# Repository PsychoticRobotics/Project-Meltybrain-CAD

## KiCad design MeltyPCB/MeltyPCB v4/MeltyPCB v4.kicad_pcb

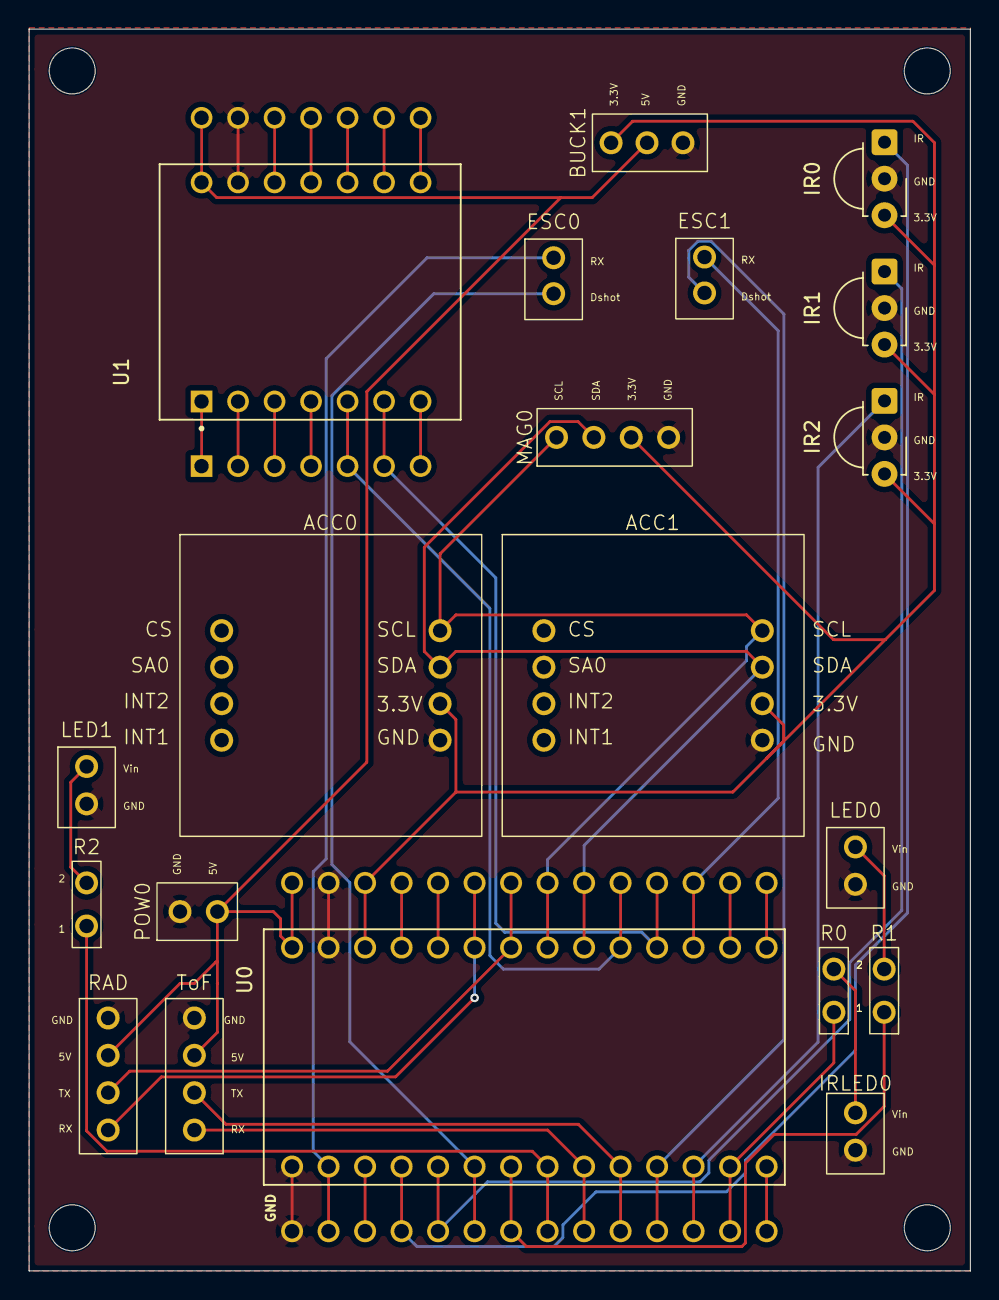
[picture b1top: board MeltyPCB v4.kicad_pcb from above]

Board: 2 copper layers, 65.5 x 86.4 mm, 20 parts (0 on the bottom side), 21 nets.

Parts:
ACC0, ACC1: Accelerometer; Accelerometer (Through Holes)
BUCK1: Buck Converter
ESC0, ESC1: Vortex ESC
IR0, IR1, IR2: TSOP384xx; Vishay_MINICAST-3Pin
IRLED0: IR LED; LED
LED0, LED1: LED
MAG0: Magnetometer
POW0: Power
R0, R1, R2: 470 Ohm; Resistor
RAD: Radio Receiver; Receiver
ToF: TFmini IR Receiver; Receiver
U0: Teensy 4.0; Teensy 4.0 (Simplified) (Extra Holes)
U1: XIAO_ESP32_S3; XIAO_ESP32_S3 (Extra Holes)

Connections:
+3.3V: ACC0.7 (3.3V), ACC1.7 (3.3V), BUCK1.1 (3.3V), IR0.3 (Vs), IR1.3 (Vs), IR2.3 (Vs), MAG0.3 (3.3V), U0.3.3V_2
+5V: BUCK1.2 (5V), POW0.1 (5V), RAD.2 (5V), ToF.2 (5V), U0.VIN, U1.14 (5V)
/Dshot0: ESC0.2 (Dshot), U0.4
/Dshot1: ESC1.2 (Dshot), U0.9
/IR0: IR0.1 (OUT), U0.2
/IR1: IR1.1 (OUT), U0.3
/IR2: IR2.1 (OUT), U0.10
/IRLED: IRLED0.1 (Vin), R0.1, R0.2, U0.11
/LED0: LED0.1 (Vin), R1.1, R1.2, U0.5
/LED1: LED1.1 (Vin), R2.1, R2.2, U0.6
/RX1: ESC0.1 (RX), U0.0
/RX2: ToF.4 (RX), U0.7
/RX3: ESC1.1 (RX), U0.15
/RX5: RAD.4 (RX), U0.21
/SCL0: ACC0.5 (SCL), ACC1.5 (SCL), MAG0.1 (SCL), U0.19
/SCL1: U0.16, U1.6 (D5/GPIO6)
/SDA0: ACC0.6 (SDA), ACC1.6 (SDA), MAG0.2 (SDA), U0.18
/SDA1: U0.17, U1.5 (D4/GPIO5)
/TX2: ToF.3 (TX), U0.8
/TX5: RAD.3 (TX), U0.20
GND: ACC0.8 (GND), ACC1.8 (GND), BUCK1.3 (GND), IR0.2 (GND), IR1.2 (GND), IR2.2 (GND), IRLED0.2 (GND), LED0.2 (GND), LED1.2 (GND), MAG0.4 (GND), POW0.2 (GND), RAD.1 (GND), ToF.1 (GND), U0.G1, U0.G3, U1.13 (GND)

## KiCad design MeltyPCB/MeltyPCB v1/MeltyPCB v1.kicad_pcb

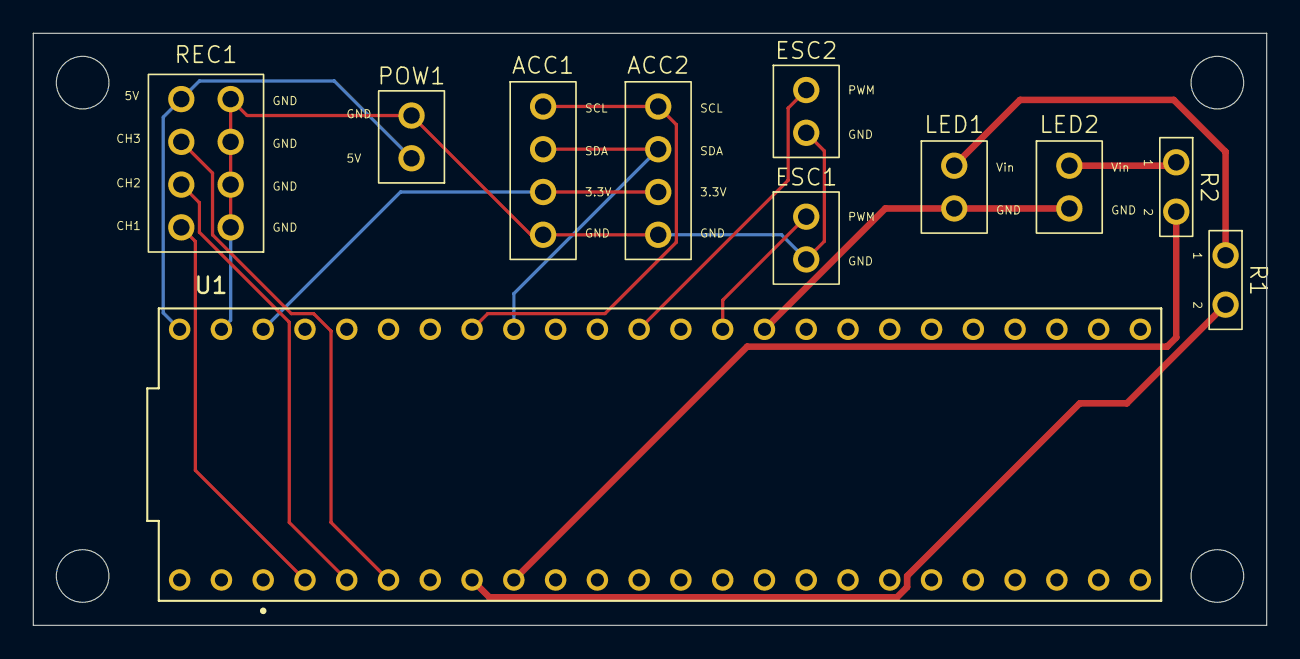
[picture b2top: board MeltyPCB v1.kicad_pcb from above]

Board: 2 copper layers, 75.0 x 36.0 mm, 11 parts (0 on the bottom side), 12 nets.

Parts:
ACC1, ACC2: Accelerometer
ESC1, ESC2: ESC
LED1, LED2: LED
POW1: Power
R1, R2: 470 Ohm; Resistor
REC1: Reciever
U1: DEV-16771 (Teensy 4.1); Teensy 4.1 (Through Holes) (Simplified)

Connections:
+3V3: ACC1.3 (3.3V), ACC2.3 (3.3V), U1.3.3V_1 (3.3V), U1.3.3V_2 (3.3V)
+5V: POW1.1 (5V), REC1.4 (5V)
/CH1: REC1.1 (CH1), U1.2 (OUT2)
/CH2: REC1.2 (CH2), U1.3 (LRCLK2)
/CH3: REC1.3 (CH3), U1.4 (BCLK2)
/ESC1: ESC1.1 (PWM), U1.13 (SCK)
/ESC2: ESC2.1 (PWM), U1.15 (A1)
/LED1: LED1.1 (Vin), R1.1, R1.2, U1.6 (OUT1D)
/LED2: LED2.1 (Vin), R2.1, R2.2, U1.7 (RX2)
/SCL: ACC1.1 (SCL), ACC2.1 (SCL), U1.19 (A5)
/SDA: ACC1.2 (SDA), ACC2.2 (SDA), U1.18 (A4)
GND: ACC1.4 (GND), ACC2.4 (GND), ESC1.2 (GND), ESC2.2 (GND), LED1.2 (GND), LED2.2 (GND), POW1.2 (GND), REC1.5 (GND), REC1.6 (GND), REC1.7 (GND), REC1.8 (GND), U1.GND1 (GND), U1.GND2 (GND), U1.GND3 (GND)

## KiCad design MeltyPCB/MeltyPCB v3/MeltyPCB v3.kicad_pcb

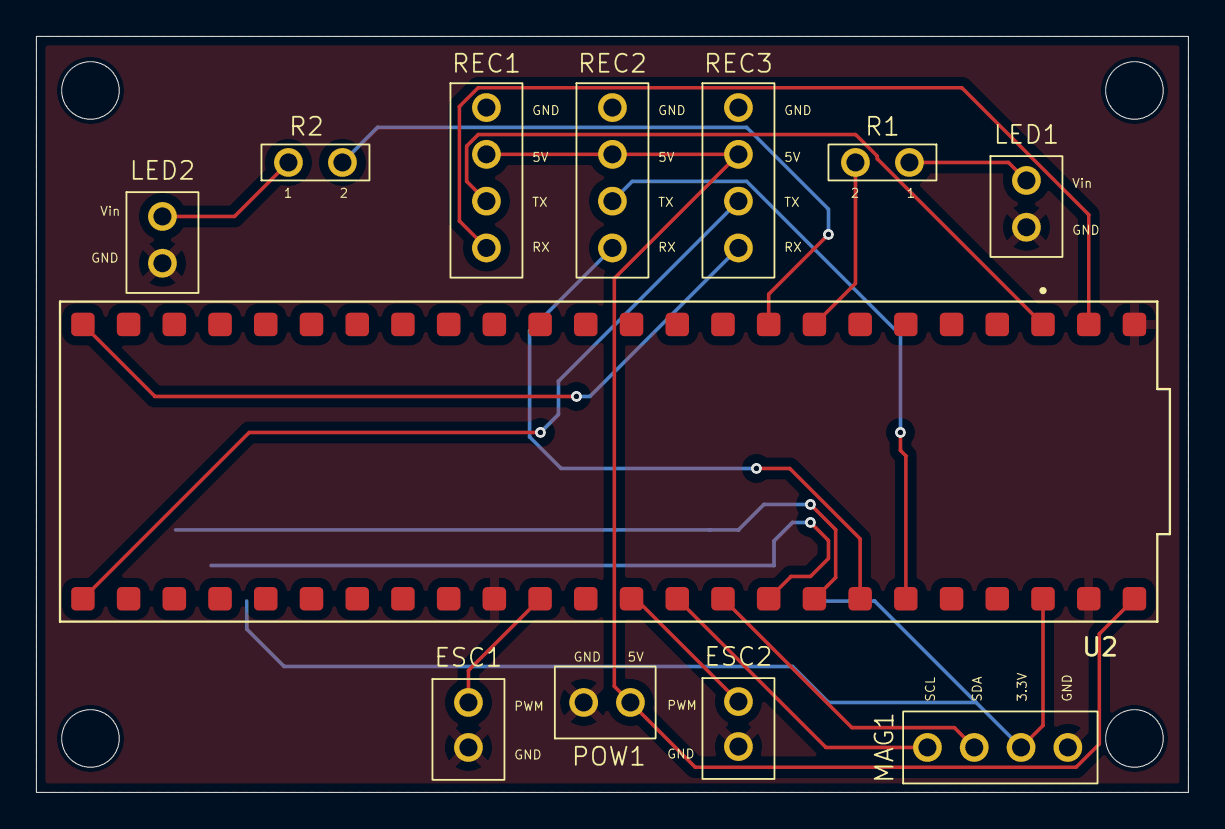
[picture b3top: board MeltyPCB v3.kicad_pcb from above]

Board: 2 copper layers, 64.0 x 42.0 mm, 14 parts (0 on the bottom side), 17 nets.

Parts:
ACC1, ACC2: Accelerometer
ESC1, ESC2: ESC
LED1, LED2: LED
MAG1: Magnetometer
POW1: Power
R1, R2: 470 Ohm; Resistor
REC1, REC2, REC3: Receiver
U2: DEV-16771 (Teensy 4.1); Teensy 4.1 (Pads) (Simplified)

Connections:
+3.3V: ACC1.7 (3.3V), ACC2.7 (3.3V), MAG1.3 (3.3V), U2.3.3V_1 (3.3V), U2.3.3V_2 (3.3V)
+5V: POW1.1 (5V), REC1.2 (5V), REC2.2 (5V), REC3.2 (5V), U2.VIN
/ESC1: ESC1.1 (PWM), U2.13 (SCK)
/ESC2: ESC2.1 (PWM), U2.15 (A1)
/LED1: LED1.1 (Vin), R1.1, R1.2, U2.6 (OUT1D)
/LED2: LED2.1 (Vin), R2.1, R2.2, U2.7 (RX2)
/RX: REC1.4 (RX), U2.0 (RX1)
/RX5: REC2.4 (RX), U2.20 (A6)
/RX6: REC3.4 (RX), U2.32 (OUT1B)
/SCL: ACC1.5 (SCL), ACC2.5 (SCL), U2.19 (A5)
/SCL2: MAG1.1 (SCL), U2.16 (A2)
/SDA: ACC1.6 (SDA), ACC2.6 (SDA), U2.18 (A4)
/SDA2: MAG1.2 (SDA), U2.17 (A3)
/TX: REC1.3 (TX), U2.1 (TX1)
/TX5: REC2.3 (TX), U2.21 (A7)
/TX6: REC3.3 (TX), U2.33 (MCLK2)
GND: ACC1.8 (GND), ACC2.8 (GND), ESC1.2 (GND), ESC2.2 (GND), LED1.2 (GND), LED2.2 (GND), MAG1.4 (GND), POW1.2 (GND), REC1.1 (GND), REC2.1 (GND), REC3.1 (GND), U2.GND1 (GND), U2.GND2 (GND), U2.GND3 (GND)

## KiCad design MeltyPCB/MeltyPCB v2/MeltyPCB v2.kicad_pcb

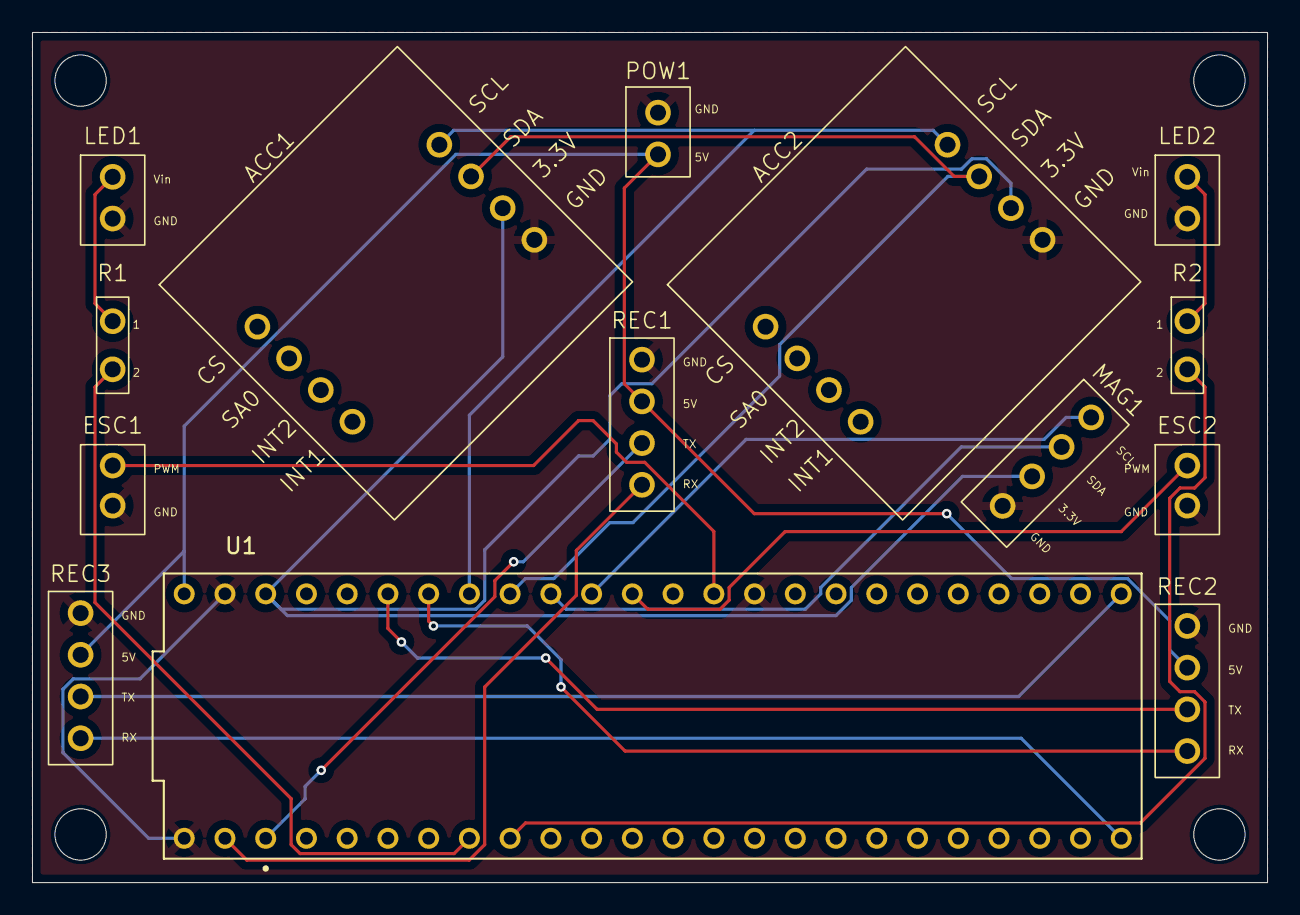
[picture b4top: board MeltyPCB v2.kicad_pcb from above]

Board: 2 copper layers, 77.0 x 53.0 mm, 14 parts (0 on the bottom side), 17 nets.

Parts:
ACC1, ACC2: Accelerometer; Accelerometer (v2)
ESC1, ESC2: ESC
LED1, LED2: LED
MAG1: Magnetometer
POW1: Power
R1, R2: 470 Ohm; Resistor
REC1, REC2, REC3: Receiver
U1: DEV-16771 (Teensy 4.1); Teensy 4.1 (Through Holes) (Simplified)

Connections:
+3.3V: ACC1.7 (3.3V), ACC2.7 (3.3V), MAG1.3 (3.3V), U1.3.3V_1 (3.3V), U1.3.3V_2 (3.3V)
+5V: POW1.1 (5V), REC1.2 (5V), REC2.2 (5V), REC3.2 (5V), U1.VIN
/ESC1: ESC1.1 (PWM), U1.13 (SCK)
/ESC2: ESC2.1 (PWM), U1.15 (A1)
/LED1: LED1.1 (Vin), R1.1, R1.2, U1.6 (OUT1D)
/LED2: LED2.1 (Vin), R2.1, R2.2, U1.7 (RX2)
/RX: REC1.4 (RX), U1.0 (RX1)
/RX5: REC2.4 (RX), U1.20 (A6)
/RX6: REC3.4 (RX), U1.32 (OUT1B)
/SCL: ACC1.5 (SCL), ACC2.5 (SCL), U1.19 (A5)
/SCL2: MAG1.1 (SCL), U1.16 (A2)
/SDA: ACC1.6 (SDA), ACC2.6 (SDA), U1.18 (A4)
/SDA2: MAG1.2 (SDA), U1.17 (A3)
/TX: REC1.3 (TX), U1.1 (TX1)
/TX5: REC2.3 (TX), U1.21 (A7)
/TX6: REC3.3 (TX), U1.33 (MCLK2)
GND: ACC1.8 (GND), ACC2.8 (GND), ESC1.2 (GND), ESC2.2 (GND), LED1.2 (GND), LED2.2 (GND), MAG1.4 (GND), POW1.2 (GND), REC1.1 (GND), REC2.1 (GND), REC3.1 (GND), U1.GND1 (GND), U1.GND2 (GND), U1.GND3 (GND)

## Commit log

2026-05-24 Add files via upload
    This is what the new motor shafts was based on. Here is the link: https://maximizermerch.com/products/shaft
2026-05-24 Add OriginalKakeShaft.step file
2026-05-24 Add files via upload
    Filler for now
2026-05-24 Add files via upload
    https://innov8tivedesigns.com/badass-2320-1860kv-brushless-motor.html
2026-05-24 Rename Shell Design TPU April 2026 2.step to Old Designs/Shell Design TPU April 2026 2.step
2026-05-24 Rename Shell Design TPU April 2026.step to Old Designs/Shell Design TPU April 2026.step
2026-05-24 Add files via upload
    From Atharv
2026-05-24 Add files via upload
    From Jayden
2026-05-24 Rename Old Designs/48mm Cleat 18Spikes.STEP to Old Designs/Wheels/48mm Cleat 18Spikes.STEP
2026-06-07 Rename Small Cleat.f3d to Cleats/Small Cleat.f3d
2026-06-07 Rename Small Cleat.step to Cleats/Small Cleat.step
2026-06-07 Rename Bidirectional Cleat with Parameters.f3d to Cleats/Bidirectional Cleat with Parameters.f3d
2026-06-07 Rename Bidirectional Cleat with Parameters.step to Cleats/Bidirectional Cleat with Parameters.step
2026-06-07 Rename Unidirectional Cleat with Parameters.f3d to Cleats/Unidirectional Cleat with Parameters.f3d
2026-06-07 Rename Unidirectional Cleat with Parameters.step to Cleats/Unidirectional Cleat with Parameters.step
2026-06-07 Rename Asymmetric Ring.step to Rings/Asymmetric Ring.step
2026-06-07 Rename Symmetric Ring.step to Rings/Symmetric Ring.step
2026-06-07 Rename NewReplacementShaft.step to Hubmotor/NewReplacementShaft.step
2026-06-07 Rename Hubmotor/NewReplacementShaft.step to Hubmotor/Shaft/NewReplacementShaft.step
2026-06-08 Added all current (v1 to v4) pcb files (project, schematic, gbr, drill, etc).
2026-06-08 Added current KiCad libraries for PCB design
2026-06-12 Updated MeltyPCB v4 + Kicad Libraries
